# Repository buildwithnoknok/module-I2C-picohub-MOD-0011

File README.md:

# module-I2C-picohub-MOD-0011 — noknok PicoHub

**noknok ID: MOD-0011.** The noknok PicoHub: a carrier board for the Raspberry Pi Pico 2 W (the noknok
brain) with its own power manager. Status: rev 1.0 built and brought up (October 2026); power-manager
firmware v0.3.1, updatable over I2C from the brain (noknok I2C bootloader, flash layout 3).

## What it is

- **Power in:** USB-C on J1, any charger. A plain 5 V adapter runs the board (enough for small
  products); a USB-PD charger is asked for 9 V by default and up to 20 V / 3 A (60 W, any ordinary
  cable) when the load or a mezzanine needs it.
- **Power manager:** a CH32X035 that negotiates USB-PD, switches every rail, watches input current,
  temperature and the 5 V rail, and protects the board. To the brain it is an ordinary noknok I2C
  module (type `0x07`) on bus A. The board also works with no firmware on it, at 5 V.
- **Ports:** four Qwiic / STEMMA QT compatible I2C ports on two switchable buses (J3/J4 bus A,
  J5/J6 bus B, 3.3 V), a switched 5 V USB host port (J2, USB 2.0 full speed via the Pico's PIO-USB),
  and a bottom-side four-cluster pogo-pad interface for swappable **mezzanine** boards (raw PD power,
  switched 5 V, I2C, SPI, USB).
- Single-sided assembly, flat bottom, 80 × 40 mm, no electrolytic capacitors.

## Repo contents

| Path | Contents |
| --- | --- |
| `docs/spec.md` | The specification: power tree and budgets, X035 and Pico pin maps (as built), socket overview (§5b: voltage, current and what can be switched per connector), the **mezzanine interface** (§6, frozen: pin map, geometry, design rules), key parts |
| `hardware/kicad/` | KiCad project: schematic (3 sheets) and PCB. Custom symbols and footprints are embedded; the shared noknok KiCad library is in the [Ecosystem](https://github.com/buildwithnoknok/Ecosystem) repo (`electrical/`) |
| `hardware/MOD-0011-schematic.pdf` | Schematic as PDF |
| `hardware/MOD-0011-bom.csv` | Bill of materials: designators, manufacturer part numbers, LCSC codes |
| `firmware/` | Power-manager firmware (ch32fun): source, binaries, `index.json` for updates, test and debug tools. **The I2C command map is in [`firmware/readme.md`](firmware/readme.md).** `firmware/bringup/` holds the bring-up and diagnostics firmware |
| `mechanical/housing.json` | Housing profile (outline, mounting holes, connector positions and exits, heights, vent) for the [noknok housing configurator](https://buildwithnoknok.github.io/housing-configurator/), taken from the rev 1.0 KiCad PCB |
| `CHANGELOG.md` | Version history |

## Using it

- Brain pins (set in the brain's `settings.toml`): I2C bus A = GP10 (SDA) / GP11 (SCL), bus B =
  GP20 / GP21, PIO-USB = GP0 (D+) / GP1 (D−).
- The brain library `noknok.py` ([brain-Pico](https://github.com/buildwithnoknok/brain-Pico))
  finds the power manager during enumeration like any other module and offers it as `c.picohub`
  (`noknok.py` 1.16+): `status()`, `source_caps()`, `set_rail()`, `cycle_rail()`, `reset_pico()`,
  `set_min_input_voltage()`, `clear_faults()`. API: brain-Pico README → *noknok PicoHub power
  manager*; the protocol underneath: [`firmware/readme.md`](firmware/readme.md) → *I2C interface*.
- Designing a mezzanine: start with `docs/spec.md` §6. A mezzanine powered from cluster A must gate its
  load with MEZZ_EN and start safely on anything from 5 to 20 V.

## License

- Firmware / code: MIT — see [LICENSE](LICENSE).
- Hardware (schematics, PCB layout, fab files, docs): CC BY-SA 4.0 — see [LICENSE-hardware](LICENSE-hardware).
- `firmware/src/usbpd.h` is adapted from [ch32fun](https://github.com/cnlohr/ch32fun) (MIT).

## Trademarks

**noknok** is a registered trademark in Switzerland (Swissreg 1300007033).

Qwiic is a registered trademark of SparkFun Electronics, Inc. STEMMA QT is a trademark of Adafruit
Industries, LLC. Raspberry Pi and Pico are trademarks of Raspberry Pi Ltd. They are named here only to
state compatibility - noknok is not affiliated with, endorsed by, or sponsored by these companies.

## Safety & Liability

noknok hardware is an electronic device and a DIY/maker kit. You assemble, modify, flash, power, and
operate it at your own risk, and it is provided as is, without warranty. This board handles up to
20 V / 3 A. See the full notice: [License, Safety & Liability](https://buildwithnoknok.github.io/safety-and-license/).

Built with the help of AI. More about how noknok uses AI: [buildwithnoknok.github.io/safety-and-license](https://buildwithnoknok.github.io/safety-and-license/).

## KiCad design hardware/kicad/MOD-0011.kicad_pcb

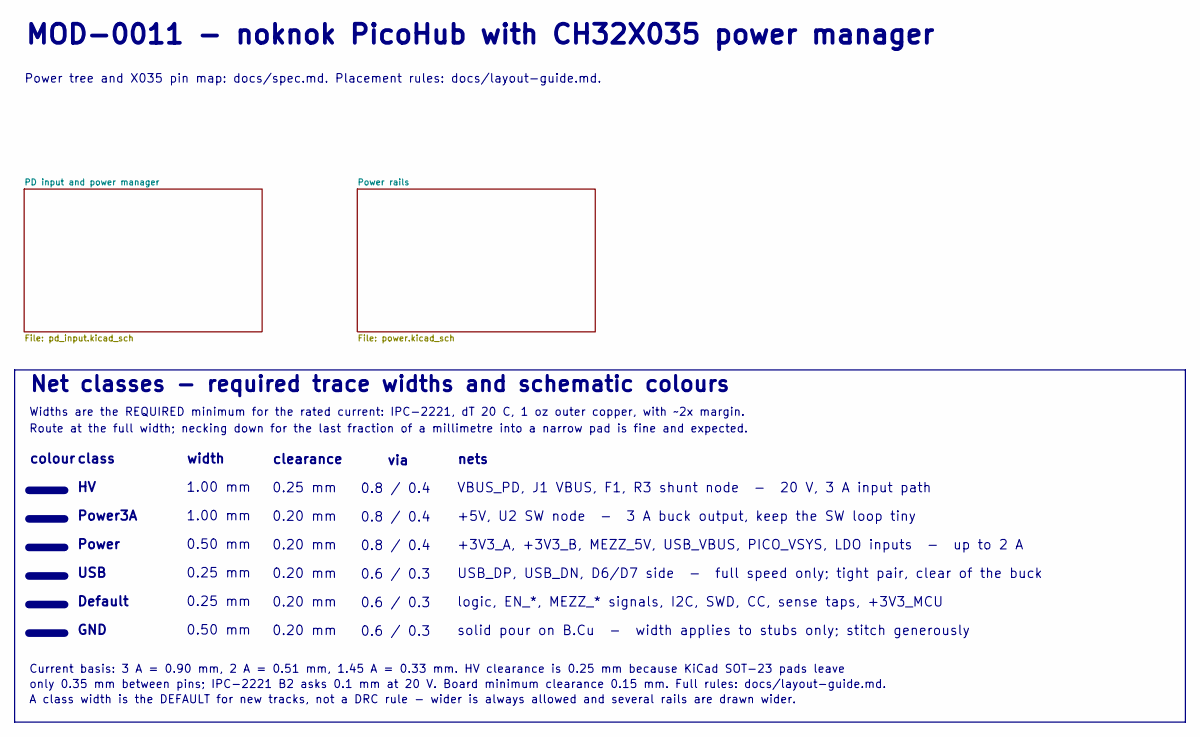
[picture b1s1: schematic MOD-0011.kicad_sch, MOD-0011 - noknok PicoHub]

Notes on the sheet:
Current basis: 3 A = 0.90 mm, 2 A = 0.51 mm, 1.45 A = 0.33 mm. HV clearance is 0.25 mm because KiCad SOT-23 pads leave
width
Power tree and X035 pin map: docs/spec.md. Placement rules: docs/layout-guide.md.
Net classes - required trace widths and schematic colours
USB
0.6 / 0.3
GND
USB_DP, USB_DN, D6/D7 side - full speed only; tight pair, clear of the buck
solid pour on B.Cu - width applies to stubs only; stitch generously
0.20 mm
class
+5V, U2 SW node - 3 A buck output, keep the SW loop tiny
1.00 mm
Default
A class width is the DEFAULT for new tracks, not a DRC rule - wider is always allowed and several rails are drawn wider.
VBUS_PD, J1 VBUS, F1, R3 shunt node - 20 V, 3 A input path
0.50 mm
0.25 mm
MOD-0011 - noknok PicoHub with CH32X035 power manager
clearance
via
+3V3_A, +3V3_B, MEZZ_5V, USB_VBUS, PICO_VSYS, LDO inputs - up to 2 A
0.8 / 0.4
colour
logic, EN_*, MEZZ_* signals, I2C, SWD, CC, sense taps, +3V3_MCU
Power3A
nets
only 0.35 mm between pins; IPC-2221 B2 asks 0.1 mm at 20 V. Board minimum clearance 0.15 mm. Full rules: docs/layout-guide.md.
Widths are the REQUIRED minimum for the rated current: IPC-2221, dT 20 C, 1 oz outer copper, with ~2x margin.
Power
Route at the full width; necking down for the last fraction of a millimetre into a narrow pad is fine and expected.

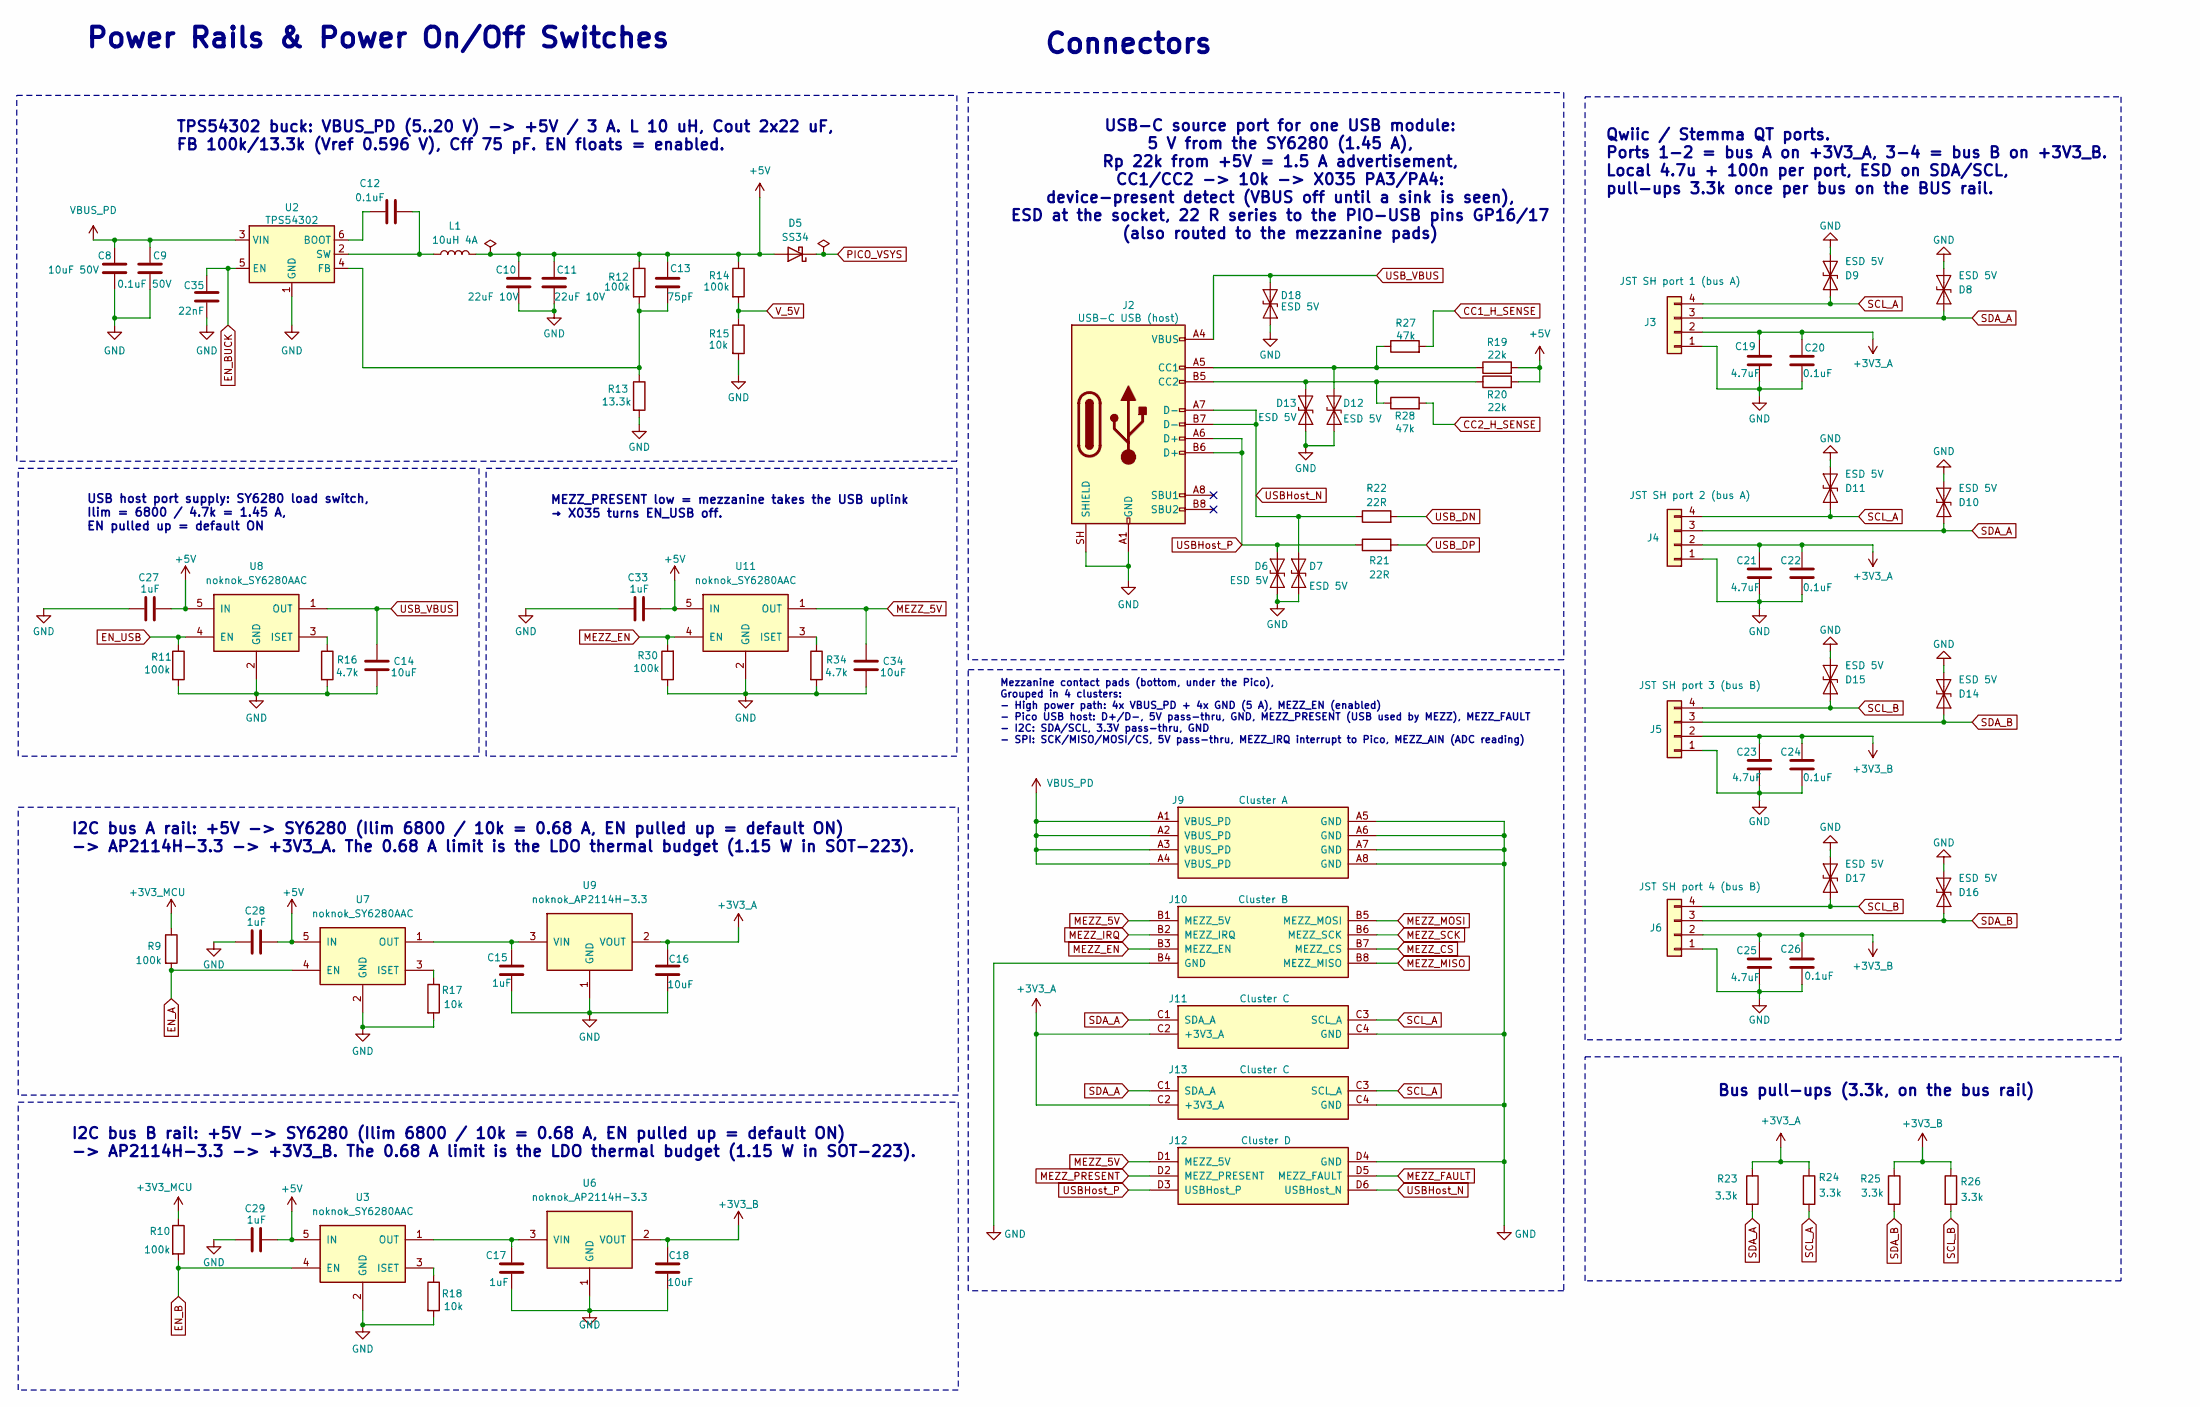
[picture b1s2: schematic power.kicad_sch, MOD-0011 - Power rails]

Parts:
C8: 10uF 50V; C_1210_3225Metric; LCSC Part # C138687
C9: 0.1uF 50V; C_0603_1608Metric; LCSC Part # C14663
C10, C11: 22uF 10V; C_0805_2012Metric; LCSC Part # C29277
C12, C20, C22, C24, C26: 0.1uF; C_0603_1608Metric; LCSC Part # C14663
C13: 75pF; C_0603_1608Metric; LCSC Part # C1681
C14, C16, C18, C34: 10uF; C_0805_2012Metric; LCSC Part # C15850
C15, C17, C27, C28, C29, C33: 1uF; C_0603_1608Metric; LCSC Part # C5199872
C19, C21, C23, C25: 4.7uF; C_0805_2012Metric; LCSC Part # C1779
C35: 22nF; C_0603_1608Metric; LCSC Part # C21122
D5: SS34; D_SMA; LCSC Part # C8678
D6, D7, D8, D9, D10, D11, D12, D13, D14, D15, D16, D17, D18: ESD 5V; D_SOD-923; LCSC Part # C111566
J2: USB-C USB (host); USB_C_Receptacle_HRO_TYPE-C-31-M-12; LCSC Part # C165948
J3: JST SH port 1 (bus A); JST_SH_SM04B-SRSS-TB_1x04-1MP_P1.00mm_Horizontal; LCSC Part # C160404
J4: JST SH port 2 (bus A); JST_SH_SM04B-SRSS-TB_1x04-1MP_P1.00mm_Horizontal; LCSC Part # C160404
J5: JST SH port 3 (bus B); JST_SH_SM04B-SRSS-TB_1x04-1MP_P1.00mm_Horizontal; LCSC Part # C160404
J6: JST SH port 4 (bus B); JST_SH_SM04B-SRSS-TB_1x04-1MP_P1.00mm_Horizontal; LCSC Part # C160404
J9: Cluster A; noknok_Mezzanine_A_Pads_M2.5
J10: Cluster B; noknok_Mezzanine_B_Pads_M2.5
J11, J13: Cluster C; noknok_Mezzanine_C_Pads_M2.5
J12: Cluster D; noknok_Mezzanine_D_Pads_M2.5
L1: 10uH 4A; L_Chilisin_BMRx00060630; LCSC Part # C2981193
R9, R10, R11, R12, R14, R30: 100k; R_0603_1608Metric; LCSC Part # C25803
R13: 13.3k; R_0603_1608Metric; LCSC Part # C25952
R15, R17, R18: 10k; R_0603_1608Metric; LCSC Part # C25804
R16, R34: 4.7k; R_0603_1608Metric; LCSC Part # C23162
R19, R20: 22k; R_0603_1608Metric; LCSC Part # C31850
R21, R22: 22R; R_0603_1608Metric; LCSC Part # C23345
R23, R24, R25, R26: 3.3k; R_0603_1608Metric; LCSC Part # C22978
R27, R28: 47k; R_0603_1608Metric; LCSC Part # C25819
U2: TPS54302; TSOT-23-6; LCSC Part # C311983
U3, U7, U8, U11: noknok_SY6280AAC; SOT-23-5; LCSC Part # C55136
U6, U9: noknok_AP2114H-3.3; SOT-223-3_TabPin2; LCSC Part # C150716

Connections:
+3V3_A: C16.1, C19.1, C20.1, C21.1, C22.1, J3.2, J4.2, J11.C2 (+3V3_A), J13.C2 (+3V3_A), R23.1, R24.1, U9.2 (VOUT)
+3V3_B: C18.1, C23.1, C24.1, C25.1, C26.1, J5.2, J6.2, R25.1, R26.1, U6.2 (VOUT)
+3V3_MCU: R9.1, R10.1; also elsewhere on the board
CC1_H_SENSE: R27.2; also elsewhere on the board
CC2_H_SENSE: R28.2; also elsewhere on the board
EN_A: R9.2, U7.4 (EN); also elsewhere on the board
EN_B: R10.2, U3.4 (EN); also elsewhere on the board
EN_BUCK: C35.1, U2.5 (EN); also elsewhere on the board
EN_USB: R11.1, U8.4 (EN); also elsewhere on the board
MEZZ_5V: C34.2, J10.B1 (MEZZ_5V), J12.D1 (MEZZ_5V), U11.1 (OUT)
MEZZ_CS: J10.B7 (MEZZ_CS); also elsewhere on the board
MEZZ_EN: J10.B3 (MEZZ_EN), R30.2, U11.4 (EN); also elsewhere on the board
MEZZ_FAULT: J12.D5 (MEZZ_FAULT); also elsewhere on the board
MEZZ_IRQ: J10.B2 (MEZZ_IRQ); also elsewhere on the board
MEZZ_MISO: J10.B8 (MEZZ_MISO); also elsewhere on the board
MEZZ_MOSI: J10.B5 (MEZZ_MOSI); also elsewhere on the board
MEZZ_PRESENT: J12.D2 (MEZZ_PRESENT); also elsewhere on the board
MEZZ_SCK: J10.B6 (MEZZ_SCK); also elsewhere on the board
unnamed: D12.1 (A1), J2.A5 (CC1), R19.1, R27.1
unnamed: D13.1 (A1), J2.B5 (CC2), R20.1, R28.1
unnamed: C12.1, U2.6 (BOOT)
unnamed: C13.2, R12.2, R13.1, U2.4 (FB)
unnamed: C12.2, L1.1, U2.2 (SW)
unnamed: R18.1, U3.3 (ISET)
unnamed: C17.1, U3.1 (OUT), U6.3 (VIN)
unnamed: R17.1, U7.3 (ISET)
unnamed: C15.1, U7.1 (OUT), U9.3 (VIN)
unnamed: R16.1, U8.3 (ISET)
unnamed: R34.1, U11.3 (ISET)
SCL_A: D9.1 (A1), D11.1 (A1), J3.4, J4.4, J11.C3 (SCL_A), J13.C3 (SCL_A), R24.2; also elsewhere on the board
SCL_B: D15.1 (A1), D17.1 (A1), J5.4, J6.4, R26.2; also elsewhere on the board
SDA_A: D8.1 (A1), D10.1 (A1), J3.3, J4.3, J11.C1 (SDA_A), J13.C1 (SDA_A), R23.2; also elsewhere on the board
SDA_B: D14.1 (A1), D16.1 (A1), J5.3, J6.3, R25.2; also elsewhere on the board
USBHost_N: D7.1 (A1), J2.A7 (D-), J2.B7 (D-), J12.D6 (USBHost_N), R22.1
USBHost_P: D6.1 (A1), J2.A6 (D+), J2.B6 (D+), J12.D3 (USBHost_P), R21.1
USB_DN: R22.2; also elsewhere on the board
USB_DP: R21.2; also elsewhere on the board
USB_VBUS: C14.2, D18.1 (A1), J2.A4 (VBUS), J2.A9 (VBUS), J2.B4 (VBUS), J2.B9 (VBUS), U8.1 (OUT)
V_5V: R14.2, R15.1; also elsewhere on the board

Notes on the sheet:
Connectors
TPS54302 buck: VBUS_PD (5..20 V) -> +5V / 3 A. L 10 uH, Cout 2x22 uF, FB 100k/13.3k (Vref 0.596 V), Cff 75 pF. EN floats = enabled.
Qwiic / Stemma QT ports. Ports 1-2 = bus A on +3V3_A, 3-4 = bus B on +3V3_B. Local 4.7u + 100n per port, ESD on SDA/SCL, pull-ups 3.3k once per bus on the BUS rail.
I2C bus A rail: +5V -> SY6280 (Ilim 6800 / 10k = 0.68 A, EN pulled up = default ON) -> AP2114H-3.3 -> +3V3_A. The 0.68 A limit is the LDO thermal budget (1.15 W in SOT-223).
USB-C source port for one USB module: 5 V from the SY6280 (1.45 A), Rp 22k from +5V = 1.5 A advertisement, CC1/CC2 -> 10k -> X035 PA3/PA4: device-present detect (VBUS off until a sink is seen), ESD at the socket, 22 R series to the PIO-USB pins GP16/17 (also routed to the mezzanine pads)
USB host port supply: SY6280 load switch, Ilim = 6800 / 4.7k = 1.45 A, EN pulled up = default ON
Power Rails & Power On/Off Switches
Bus pull-ups (3.3k, on the bus rail)
MEZZ_PRESENT low = mezzanine takes the USB uplink → X035 turns EN_USB off.
Mezzanine contact pads (bottom, under the Pico), Grouped in 4 clusters: - High power path: 4x VBUS_PD + 4x GND (5 A), MEZZ_EN (enabled) - Pico USB host: D+/D-, 5V pass-thru, GND, MEZZ_PRESENT (USB used by MEZZ), MEZZ_FAULT - I2C: SDA/SCL, 3.3V pass-thru, GND - SPI: SCK/MISO/MOSI/CS, 5V pass-thru, M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
I2C bus B rail: +5V -> SY6280 (Ilim 6800 / 10k = 0.68 A, EN pulled up = default ON) -> AP2114H-3.3 -> +3V3_B. The 0.68 A limit is the LDO thermal budget (1.15 W in SOT-223).

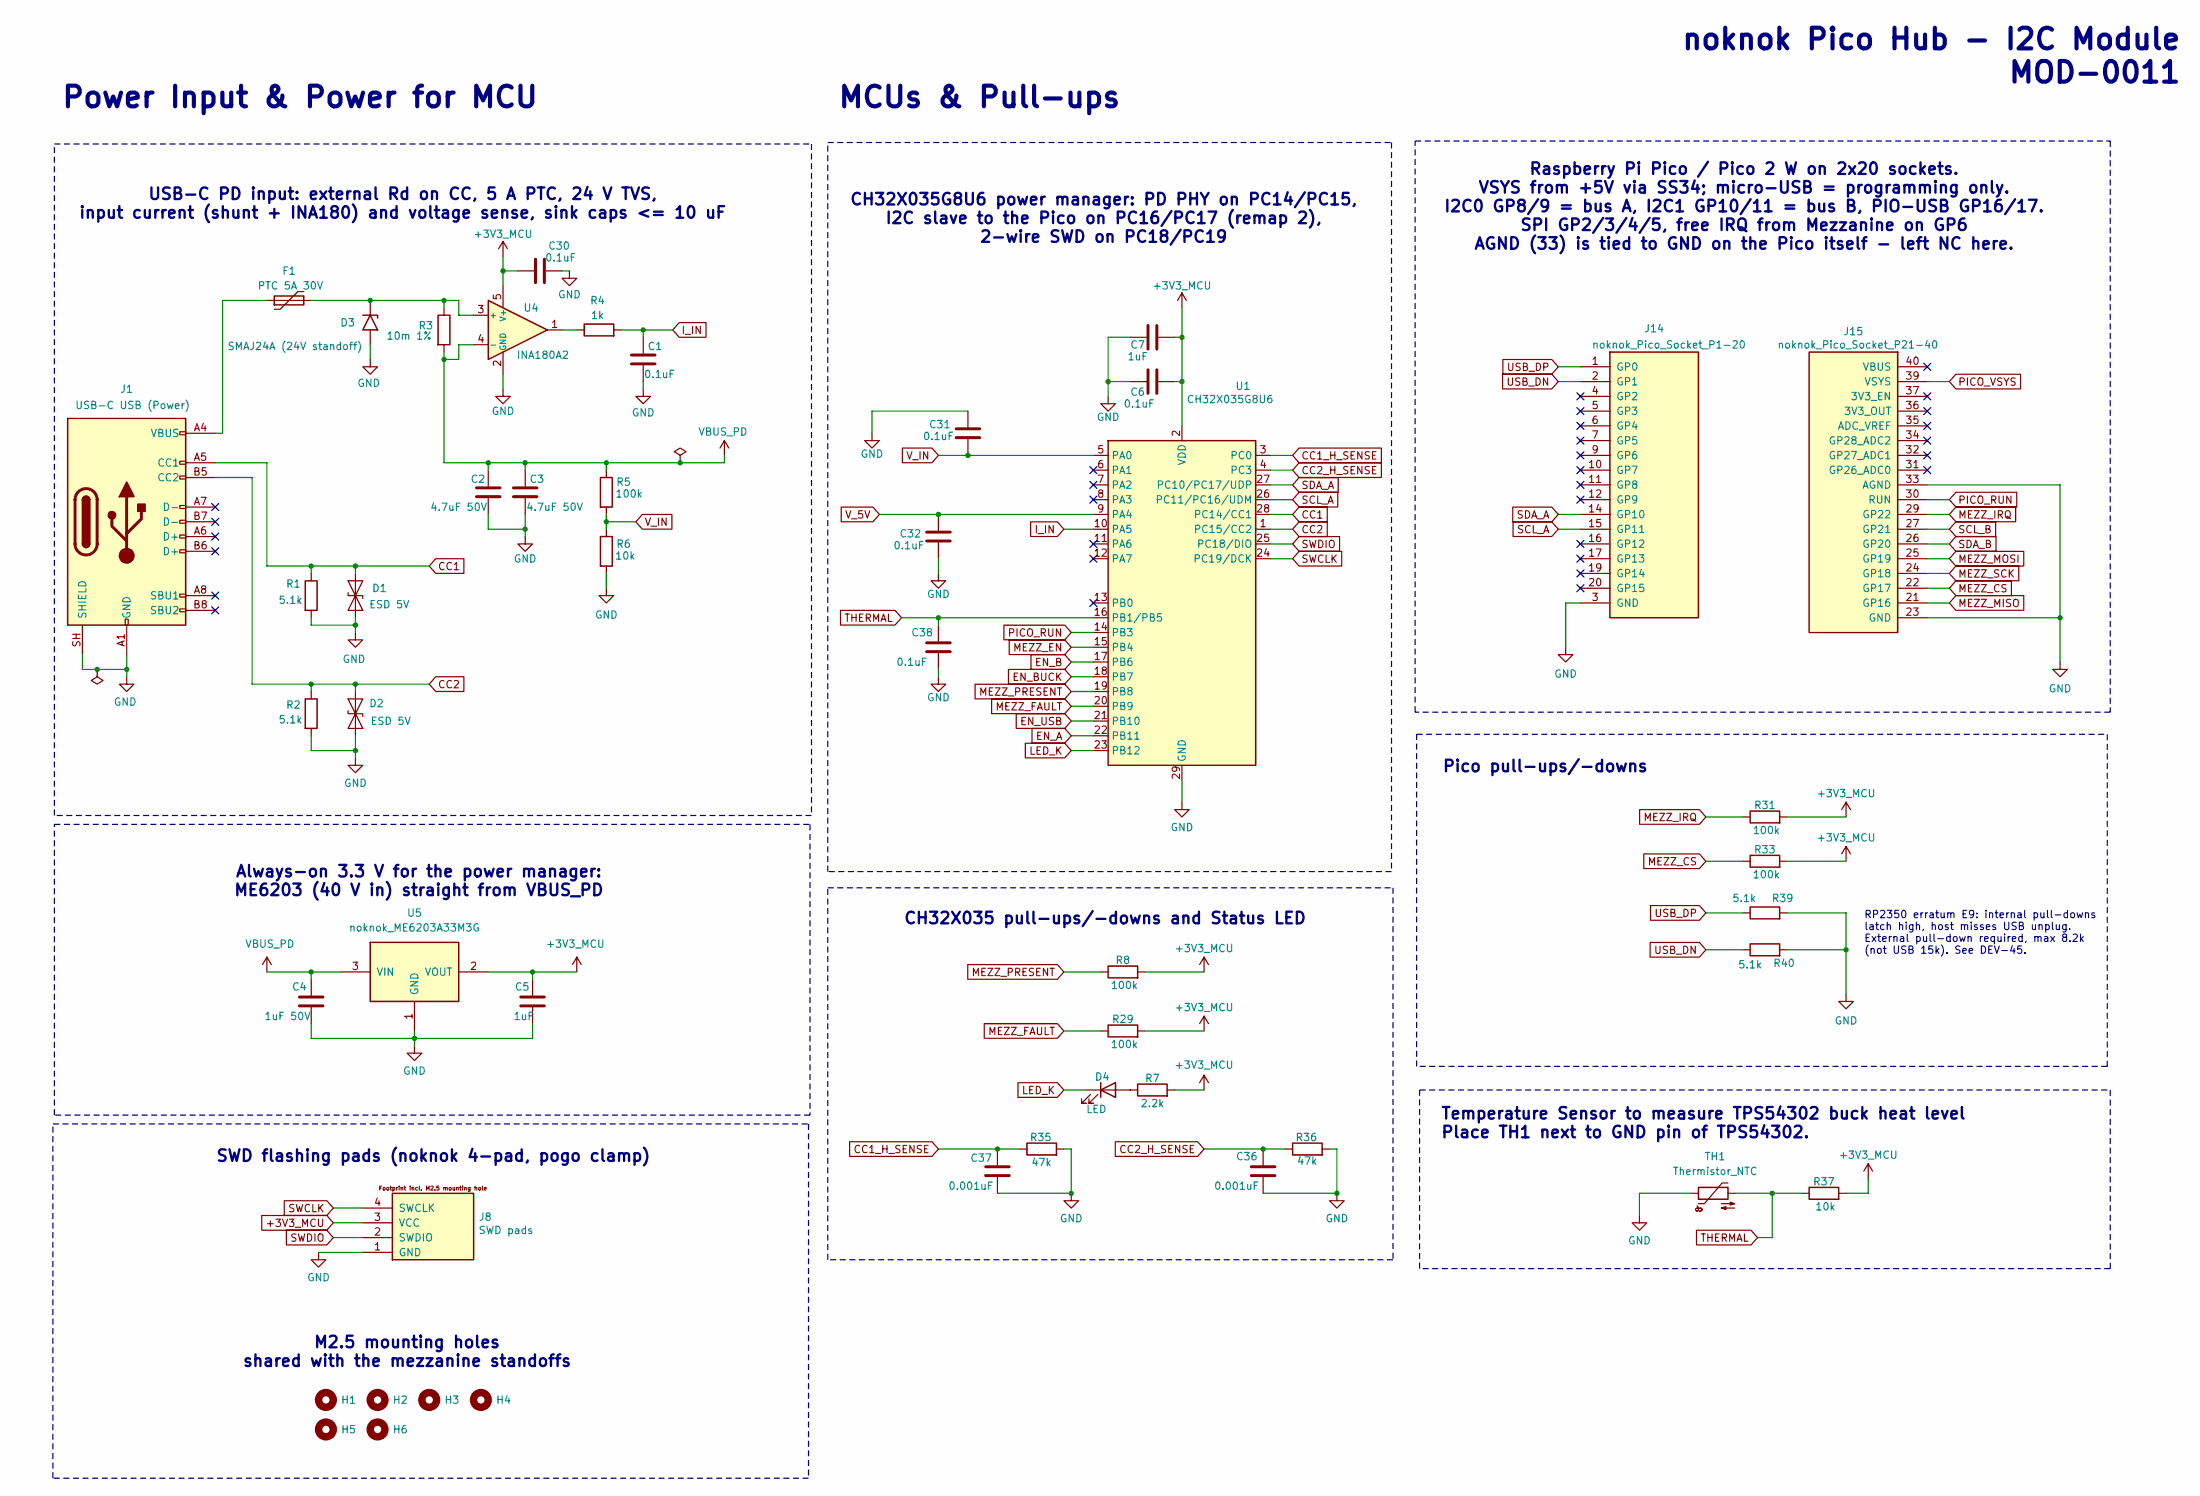
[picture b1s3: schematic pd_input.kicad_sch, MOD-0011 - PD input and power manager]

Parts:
C1, C6, C30, C31, C32, C38: 0.1uF; C_0603_1608Metric; LCSC Part # C14663
C2, C3: 4.7uF 50V; C_1206_3216Metric; LCSC Part # C51205
C4: 1uF 50V; C_0603_1608Metric; LCSC Part # C5199872
C5, C7: 1uF; C_0603_1608Metric; LCSC Part # C5199872
C36, C37: 0.001uF; C_0603_1608Metric; LCSC Part # C1588
D1, D2: ESD 5V; D_SOD-923; LCSC Part # C111566
D3: SMAJ24A (24V standoff); D_SMA; LCSC Part # C908774
D4: LED; LED_0603_1608Metric; LCSC Part # C2286
F1: PTC 5A 30V; Fuse_2920_7451Metric; LCSC Part # C19078763
H1, H2, H3, H4, H5, H6: noknok_MountingHole; noknok_MountingHole_2.5mm_M2.5
J1: USB-C USB (Power); USB_C_Receptacle_HRO_TYPE-C-31-M-12; LCSC Part # C165948
J8: SWD pads; noknok_FlashPads_USB-module_1x4_M2.5
J14: noknok_Pico_Socket_P1-20; noknok_Pico_Socket_P1-20_THT; LCSC Part # C7509519
J15: noknok_Pico_Socket_P21-40; noknok_Pico_Socket_P21-40_THT; LCSC Part # C7509519
R1, R2: 5.1k; R_0603_1608Metric; LCSC Part # C23186
R3: 10m 1%; R_2512_6332Metric; LCSC Part # C46634450
R4: 1k; R_0603_1608Metric; LCSC Part # C21190
R5, R8, R29, R31, R33: 100k; R_0603_1608Metric; LCSC Part # C25803
R6, R37: 10k; R_0603_1608Metric; LCSC Part # C25804
R7: 2.2k; R_0603_1608Metric; LCSC Part # C4190
R35, R36: 47k; R_0603_1608Metric; LCSC Part # C25819
R39, R40: 5.1k; R_0603_1608Metric; LCSC Part # C21190
TH1: Thermistor_NTC; R_0603_1608Metric; LCSC Part # C2892547
U1: CH32X035G8U6; WQFN-28-1EP_4x4mm_P0.4mm_EP2.7x2.7mm; LCSC Part # C7437027
U4: INA180A2; SOT-23-5; LCSC Part # C192764
U5: noknok_ME6203A33M3G; SOT-23; LCSC Part # C87842

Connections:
+3V3_MCU: C5.1, C6.2, C7.2, C30.1, J8.3 (VCC), R7.2, R8.2, R29.2, R31.2, R33.2, R37.2, U1.2 (VDD), U4.5 (V+), U5.2 (VOUT); also elsewhere on the board
CC1: D1.1 (A1), J1.A5 (CC1), R1.1, U1.28 (PC14/CC1)
CC1_H_SENSE: C37.1, R35.1, U1.3 (PC0); also elsewhere on the board
CC2: D2.1 (A1), J1.B5 (CC2), R2.1, U1.1 (PC15/CC2)
CC2_H_SENSE: C36.1, R36.1, U1.4 (PC3); also elsewhere on the board
EN_A: U1.22 (PB11); also elsewhere on the board
EN_B: U1.17 (PB6); also elsewhere on the board
EN_BUCK: U1.18 (PB7); also elsewhere on the board
EN_USB: U1.21 (PB10); also elsewhere on the board
I_IN: C1.1, R4.2, U1.10 (PA5)
LED_K: D4.1 (K), U1.23 (PB12)
MEZZ_CS: J15.22 (GP17), R33.1; also elsewhere on the board
MEZZ_EN: U1.15 (PB4); also elsewhere on the board
MEZZ_FAULT: R29.1, U1.20 (PB9); also elsewhere on the board
MEZZ_IRQ: J15.29 (GP22), R31.1; also elsewhere on the board
MEZZ_MISO: J15.21 (GP16); also elsewhere on the board
MEZZ_MOSI: J15.25 (GP19); also elsewhere on the board
MEZZ_PRESENT: R8.1, U1.19 (PB8); also elsewhere on the board
MEZZ_SCK: J15.24 (GP18); also elsewhere on the board
unnamed: D3.1 (A1), F1.2, R3.1, U4.3 (+)
unnamed: D4.2 (A), R7.1
unnamed: F1.1, J1.A4 (VBUS), J1.A9 (VBUS), J1.B4 (VBUS), J1.B9 (VBUS)
unnamed: R4.1, U4.1
PICO_RUN: J15.30 (RUN), U1.14 (PB3)
SCL_A: J14.15 (GP11), U1.26 (PC11/PC16/UDM); also elsewhere on the board
SCL_B: J15.27 (GP21); also elsewhere on the board
SDA_A: J14.14 (GP10), U1.27 (PC10/PC17/UDP); also elsewhere on the board
SDA_B: J15.26 (GP20); also elsewhere on the board
SWCLK: J8.4 (SWCLK), U1.24 (PC19/DCK)
SWDIO: J8.2 (SWDIO), U1.25 (PC18/DIO)
THERMAL: C38.1, R37.1, TH1.2, U1.16 (PB1/PB5)
USB_DN: J14.2 (GP1), R40.1; also elsewhere on the board
USB_DP: J14.1 (GP0), R39.1; also elsewhere on the board
V_5V: C32.2, U1.9 (PA4); also elsewhere on the board
V_IN: C31.1, R5.2, R6.1, U1.5 (PA0)

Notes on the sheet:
RP2350 erratum E9: internal pull-downs latch high, host misses USB unplug. External pull-down required, max 8.2k (not USB 15k). See DEV-45.
Temperature Sensor to measure TPS54302 buck heat level Place TH1 next to GND pin of TPS54302.
Power Input & Power for MCU
Pico pull-ups/-downs
SWD flashing pads (noknok 4-pad, pogo clamp)
CH32X035G8U6 power manager: PD PHY on PC14/PC15, I2C slave to the Pico on PC16/PC17 (remap 2), 2-wire SWD on PC18/PC19
Raspberry Pi Pico / Pico 2 W on 2x20 sockets. VSYS from +5V via SS34; micro-USB = programming only. I2C0 GP8/9 = bus A, I2C1 GP10/11 = bus B, PIO-USB GP16/17. SPI GP2/3/4/5, free IRQ from Mezzanine on GP6 AGND (33) is tied to GND on the Pico itself - left NC here.
MCUs & Pull-ups
USB-C PD input: external Rd on CC, 5 A PTC, 24 V TVS, input current (shunt + INA180) and voltage sense, sink caps <= 10 uF
M2.5 mounting holes shared with the mezzanine standoffs
CH32X035 pull-ups/-downs and Status LED
Always-on 3.3 V for the power manager: ME6203 (40 V in) straight from VBUS_PD
noknok Pico Hub - I2C Module MOD-0011

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
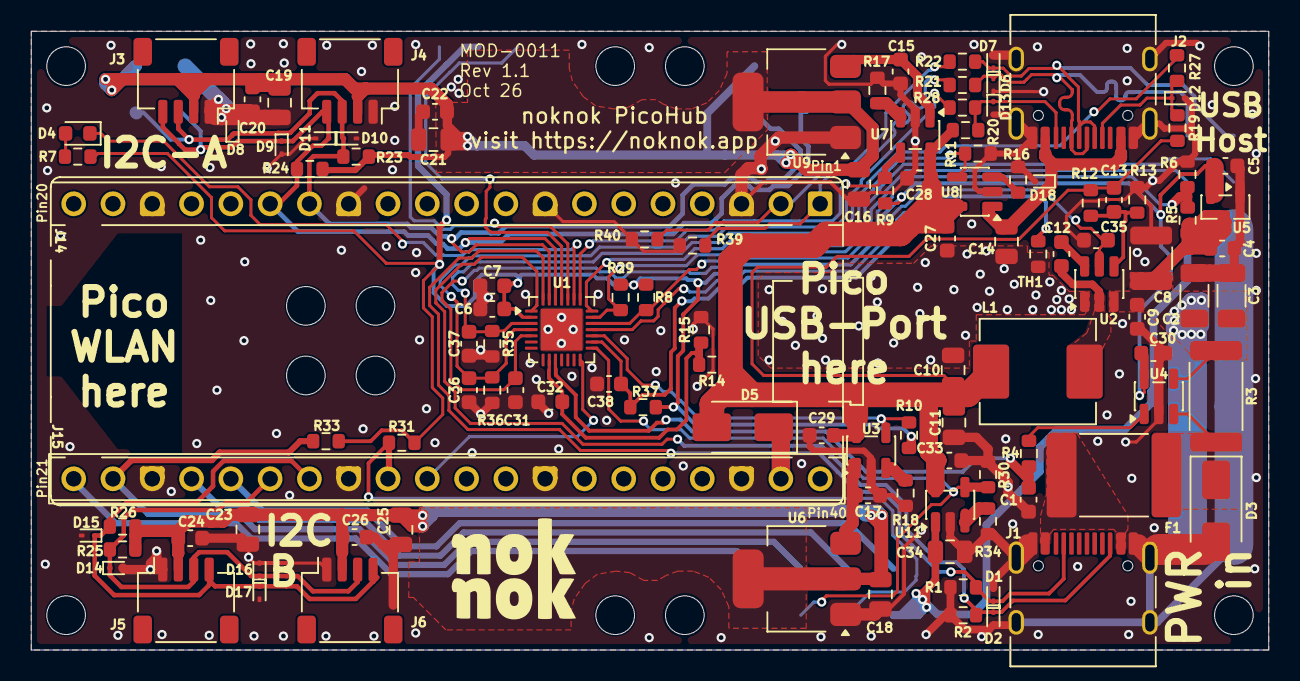
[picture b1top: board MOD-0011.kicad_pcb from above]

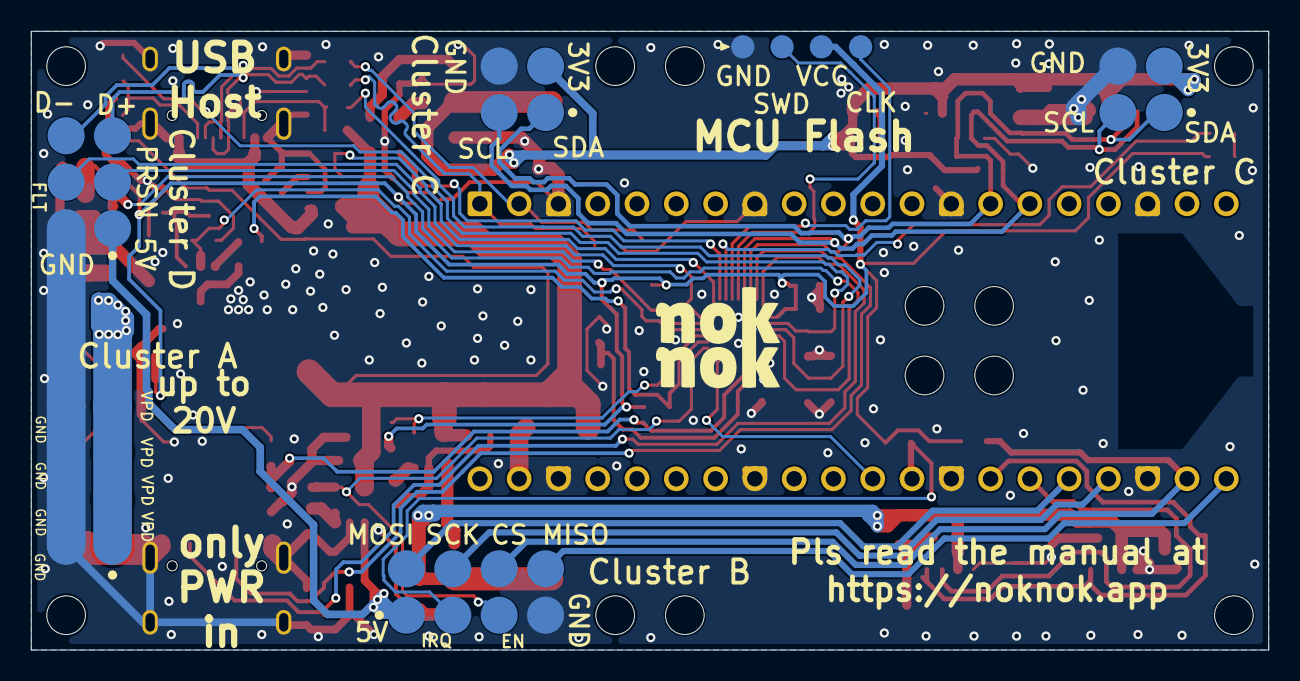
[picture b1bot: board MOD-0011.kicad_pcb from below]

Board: 2 copper layers, 80.0 x 40.0 mm, 127 parts (6 on the bottom side), 56 nets.

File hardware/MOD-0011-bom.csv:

Item #,Designator,Qty,Manufacturer,Mfg Part #,Description / Value,Vendor Part #,Note
1,"C1, C6, C9, C12, C20, C22, C24, C26, C30, C31, C32, C38",12,YAGEO,CC0603KRX7R9BB104,0.1uF ±10% 50V X7R 0603,C14663,one 50 V reel for every 0.1 uF; Samsung CL10B104KB8NNNC C1591 (16-LED board) is out of stock at LCSC today
2,"C2, C3",2,Samsung,CL31B475KBHNNNE,4.7uF ±10% 50V X7R 1206,C51205,"PD input caps (sink capacitance <= 10 uF). Moved 1210 -> 1206 on 24 Sep: same X7R/50 V, 36% less area, 45% cheaper; ~10% more DC-bias loss, irrelevant here"
3,"C4, C5, C7, C15, C17, C27, C28, C29, C33",9,Samsung,CL10B105KB8NQNC,1uF ±10% 50V X7R 0603,C5199872,C4 (ME6203 input); same reel as the other 1 uF; same part as the 16-LED board
4,C8,1,Samsung,CL32B106KBJNNNE,10uF ±10% 50V X7R 1210,C138687,buck input cap
5,"C10, C11",2,Samsung,CL21A226MPQNNNE,22uF ±20% 10V X5R 0805,C29277,buck output caps; alt FOJAN FCC0805X226M100FT C5137600 (146k stock)
6,C13,1,FH,0603CG750J500NT,75pF ±5% 50V C0G 0603,C1681,Samsung CL10C750JB8NNNC is discontinued
7,"C14, C16, C18, C34",4,Samsung,CL21A106KAYNNNE,10uF ±10% 25V X5R 0805,C15850,LDO outputs
8,"C19, C21, C23, C25",4,Samsung,CL21A475KAQNNNE,4.7uF ±10% 25V X5R 0805,C1779,port bulk caps
9,C35,1,Samsung,CL10B223KB8NNNC,22nF ±10% 50V X7R 0603,C21122,TPS54302 EN delay cap (~38 ms default-on)
10,"C36, C37",2,Samsung,CL10B102KB8NNNC,1nF ±10% 50V X7R 0603,C1588,ADC filter at PA3/PA4
11,"D1, D2, D6, D7, D8, D9, D10, D11, D12, D13, D14, D15, D16, D17, D18",15,onsemi,ESD9B5.0ST5G,"ESD TVS 5V working, SOD-923",C111566,same part as the 16-LED board
12,D3,1,GOODWORK,SMAJ24A,"TVS 24V standoff, 38.9V clamp, 400W, SMA, unidirectional",C908774,MDD C113962 out of stock; Littelfuse C148222 as a name-brand alternative
13,D4,1,Hubei KENTO,KT-0603R,LED red 0603,C2286,the noknok status LED
14,D5,1,MDD,SS34,Schottky 40V 3A SMA,C8678,VSYS OR-ing diode
15,F1,1,LUTE,2920L500/30GR,"PTC resettable fuse 5A hold, 30V, 2920",C19078763,"30 V (was 24 V): more headroom on the PD voltage steps, cheaper, 47k in stock vs 18k. Hold current derates to ~3.5 A at 60 C ambient - see spec 2.1"
16,"J1, J2",2,HRO,TYPE-C-31-M-12,"USB-C receptacle 16-pin, 20V/5A, 10k cycles",C165948,host port; PD input
17,"J3, J4, J5, J6",4,JST,SM04B-SRSS-TB(LF)(SN),JST SH 4-pin horizontal (Qwiic),C160404,same as all modules
18,"J14, J15",2,CONNFLY,DS1023-1x20SF11,"Female header 1x20, 2.54 mm, THT, 8.5 mm insulator, gold — Pico socket half (J14 = pins 1-20, J15 = pins 21-40)",C7509519,one of the two socket halves (J14/J15); the Pico 2 W (SC1633) is bought separately and plugged in. Split into two designators so the position file reports two correct centroids - JLCPCB rejected the single-footprint version.
19,L1,1,Chilisin,AMRU00060630100MA1,"10uH moulded power inductor, Isat 4A, 7.3x6.8mm",C2981193,buck inductor
20,"R1, R2, R39, R40",4,UNI-ROYAL,0603WAF5101T5E,5.1k ±1% 0603,C23186,"R1/R2 PD Rd, 1% needed. R39/R40 USB D+/D- pull-downs (rev 1.1, RP2350 erratum E9, keep <= 8.2k, DEV-45)"
21,R3,1,JIERR,JER2512F3R010,"10mOhm ±1% 3W alloy current-sense resistor 2512, ±50ppm",C46634450,input shunt for the INA180A2
22,R4,1,UNI-ROYAL,0603WAF1001T5E,1k ±1% 0603,C21190,
23,"R5, R8, R9, R10, R11, R12, R14, R29, R30, R31, R33",11,UNI-ROYAL,0603WAF1003T5E,100k ±1% 0603,C25803,1% because R5 is the buck feedback top resistor
24,"R6, R15, R17, R18, R37",5,UNI-ROYAL,0603WAF1002T5E,10k ±1% 0603,C25804,
25,R7,1,UNI-ROYAL,0603WAF2201T5E,2.2k ±1% 0603,C4190,status LED
26,R13,1,UNI-ROYAL,0603WAF1332T5E,13.3k ±1% 0603,C25952,buck feedback bottom
27,"R16, R34",2,UNI-ROYAL,0603WAF4701T5E,4.7k ±1% 0603,C23162,SY6280 Rset (1.45 A)
28,"R19, R20",2,UNI-ROYAL,0603WAF2202T5E,22k ±1% 0603,C31850,host-port Rp
29,"R21, R22",2,UNI-ROYAL,0603WAF220JT5E,22R ±1% 0603,C23345,USB D+/D- series
30,"R23, R24, R25, R26",4,UNI-ROYAL,0603WAF3301T5E,3.3k ±1% 0603,C22978,I2C pull-ups
31,"R27, R28, R35, R36",4,UNI-ROYAL,0603WAF4702T5E,47k ±1% 0603,C25819,host-port CC sense divider (R27/R28 series + R35/R36 to GND)
32,TH1,1,KUU,KNTC0603/10KF3950,"NTC thermistor 10k ±1%, B3950 (B25/85) ±1%, 0603, -40 to +125 C",C2892547,"board temperature sensor (TH1) beside U2; low leg of a 10k divider into X035 pin 16 (PB1/A9; corrected 18 Oct 2026, DEV-117)"
33,U1,1,WCH,CH32X035G8U6,"RISC-V MCU with USB-PD PHY, QFN-28",C7437027,power manager
34,U2,1,TI,TPS54302DDCR,"3A synchronous buck, 4.5-28V in, TSOT-23-6",C311983,5 V buck
35,"U3, U7, U8, U11",4,Silergy,SY6280AAC,"load switch with adjustable current limit, SOT-23-5",C55136,"USB host, bus A, bus B"
36,U4,1,TI,INA180A2IDBVR,"current-sense amplifier 50 V/V, SOT-23-5",C192764,input current
37,U5,1,Microne,ME6203A33M3G,"3.3V LDO, 40V in, SOT-23",C87842,always-on X035 supply
38,"U6, U9",2,Diodes Inc,AP2114H-3.3TRG1,"3.3V 1A LDO, SOT-223",C150716,bus A / bus B LDOs

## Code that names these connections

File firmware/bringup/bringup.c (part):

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 * power-manager firmware (DEV-85) is written:
 *
 *  1. BOOT / warm-reset test (runs by itself at power-on).
 *     PC17 is I2C SDA_A *and* the X035 BOOT-detect pin: high at reset may
 *     enter the factory bootloader. At a cold boot SDA_A's pull-up (R23 on
 *     +3V3_A) is still unpowered; at a warm reset it is not. Sequence, driven
 *     by the reset-cause flags so it needs no memory between resets:
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 *        software   -> LED 2 blinks x3, then a WATCHDOG reset (IWDG left unfed, ~5.6 s)
 *        watchdog   -> LED 3 blinks x3, then the heartbeat = PASS
 *     LED goes dark and stays dark after a reset = stuck in the bootloader = FAIL.
 *     If PC17 is LOW before a reset the test would prove nothing (bus A not
 *     powered, e.g. board fed only from the flash clamp): the LED fast-blinks
 *     and the test waits until PC17 is high.
 *
 *  2. Hardware default states: nothing below touches EN_A / EN_B / EN_USB /
 *     MEZZ_EN / EN_BUCK / PICO_RUN until a command is typed. Measure first.
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 *
 * Pin map = the board AS FABRICATED (read from hardware/kicad/MOD-0011.kicad_pcb,
 * U1 pads, 17 Oct 2026). docs/spec.md section 3 was rewritten from it on 18 Oct 2026.
 *   pin  3 PC0  A10  CC1_H_SENSE  J2 CC1 via 47k/47k        (A10/A13 to be
 *   pin  4 PC3  A13  CC2_H_SENSE  J2 CC2 via 47k/47k         confirmed: 'd')
 *   pin  5 PA0  A0   V_IN         100k/10k (x11)
 *   pin  9 PA4  A4   V_5V         100k/10k (x11)
 *   pin 10 PA5  A5   I_IN         INA180A2 on 10 mohm: 0.5 V per A
 *   pin 16 PB1  A9   THERMAL      NTC 10k B3950 (TH1) to GND, 10k (R37) to 3V3_MCU
 *   pin 14 PB3       PICO_RUN     open-drain ONLY (Pico RUN has its own pull-up)
 *   pin 15 PB4       MEZZ_EN      R30 100k pull-DOWN -> default OFF, drive high = on
 *   pin 17 PB6       EN_B         R10 100k pull-up   -> default ON, drive low = off
 *   pin 18 PB7       EN_BUCK      C35 22 nF, no pull -> buck self-starts; low = off
 *   pin 19 PB8       MEZZ_PRESENT pull-up, low = mezzanine takes the USB uplink
 *   pin 20 PB9       MEZZ_FAULT   pull-up, low = mezzanine fault
 *   pin 21 PB10      EN_USB       R11 100k pull-DOWN -> default OFF, drive high = on
 *   pin 22 PB11      EN_A         R9 100k pull-up    -> default ON, drive low = off
 *   pin 23 PB12      LED_K        status LED cathode, active LOW
 *   pin 27 PC17      SDA_A        read only here (BOOT-detect pin)
 */
#include "ch32fun.h"
#include <stdio.h>
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#define RST_LPWRF  (1u << 31)

// Port B pin numbers (all < 16, so funPinMode handles them).
#define P_PICO_RUN     PB3
#define P_MEZZ_EN      PB4
#define P_EN_B         PB6
#define P_EN_BUCK      PB7
#define P_MEZZ_PRESENT PB8
#define P_MEZZ_FAULT   PB9
#define P_EN_USB       PB10
#define P_EN_A         PB11
#define P_LED          PB12

// ADC channels
#define CH_V_IN   0
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	ADC1->CTLR2 |= ADC_ADON | ADC_EXTSEL;

	// analog mode (CFG = 0) on the six wired channels
	funPinMode( PA0, 0 ); funPinMode( PA4, 0 ); funPinMode( PA5, 0 );
	funPinMode( PB1, 0 ); funPinMode( PC0, 0 ); funPinMode( PC3, 0 );
}

static uint16_t adc_read( int ch )     // average of 16 conversions, 0..4095
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static void wait_sda_high( const char * why )
{
	if( sda_a_high() ) return;
	printf( "TEST INVALID until PC17/SDA_A is high (%s): bus A not powered? "
	        "Power the board from USB-C J1, not only from the flash clamp.\n", why );
	while( !sda_a_high() ) { led(1); Delay_Ms( 50 ); led(0); Delay_Ms( 50 ); }
	printf( "PC17 high now, continuing\n" );
}

static const char * cause_name( uint32_t f )
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// may issue on its way to the app.
#define BOOTLOG_MAGIC 0x4E4B4231u            // "NKB1"
#define BOOTLOG_MAX   16
typedef struct { uint32_t magic, count; uint32_t flags[BOOTLOG_MAX]; uint8_t pc17[BOOTLOG_MAX]; } bootlog_t;
#define BOOTLOG ((volatile bootlog_t *)0x20003000)

int main( void )
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	int cold = ( BOOTLOG->magic != BOOTLOG_MAGIC || BOOTLOG->count >= BOOTLOG_MAX );
	if( cold ) { BOOTLOG->magic = BOOTLOG_MAGIC; BOOTLOG->count = 0; }
	BOOTLOG->flags[BOOTLOG->count] = flags;
	BOOTLOG->pc17[BOOTLOG->count] = sda_a_high();
	BOOTLOG->count++;

	printf( "\nnoknok PicoHub MOD-0011 bring-up v" FW_VERSION "  reset flags 0x%08lx = %s  PC17 %d%s\n",
	        (unsigned long)flags, cause_name( flags ), sda_a_high(), cold ? "  (first boot since power-up)" : "" );
	printf( "boot log since power-up:" );
	for( uint32_t i = 0; i < BOOTLOG->count; i++ )
		printf( "  #%lu 0x%08lx %s PC17=%d", (unsigned long)i + 1, (unsigned long)BOOTLOG->flags[i],
		        cause_name( BOOTLOG->flags[i] ), BOOTLOG->pc17[i] );
	printf( "\n" );

	// On the X035 the factory bootloader runs at EVERY power-up and starts the app with a
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	{
		blink_code( 3 );
		printf( "RESET TEST PASS: power-on -> software reset -> watchdog reset, "
		        "app came back each time with PC17 high.\n" );
	}
	else if( flags & RST_SFTF )
	{
		blink_code( 2 );
		wait_sda_high( "before watchdog reset" );
		printf( "STEP 2/3 back from SOFTWARE reset. Watchdog reset in ~5.6 s (PC17 %d)\n", sda_a_high() );
		iwdg_start_unfed();
		while( 1 ) { led(1); Delay_Ms( 50 ); led(0); Delay_Ms( 450 ); }
	}
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	{
		blink_code( 1 );
		wait_sda_high( "before software reset" );
		printf( "STEP 1/3 cold start. Software reset in 3 s (PC17 %d)\n", sda_a_high() );
		Delay_Ms( 3000 );
		NVIC_SystemReset();
		while( 1 );
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
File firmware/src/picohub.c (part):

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 *   w stop feeding the watchdog (reset test)   h help
 *
 * Pin map = the board as fabricated (docs/spec.md section 3):
 *   PA0 A0 V_IN x11     PA4 A4 V_5V x11     PA5 A5 I_IN 0.5 V/A (+14 mA offset)
 *   PB1 A9 NTC TH1      PC0 A10 / PC3 A13 J2 CC1/CC2 sense, x2
 *   PB3 PICO_RUN (open-drain only)   PB4 MEZZ_EN (pull-down, drive high = on)
 *   PB6 EN_B (pull-up, drive low = off)   PB7 EN_BUCK (self-starts, drive low = off)
 *   PB8 MEZZ_PRESENT (low = present)   PB9 MEZZ_FAULT (low = fault)
 *   PB10 EN_USB (pull-down, drive high = on)   PB11 EN_A (pull-up)   PB12 LED_K (active low)
 *   PC14/PC15 USB-PD CC1/CC2 (external 5.1 k Rd)   PC16/PC17 I2C bus A (not used yet)
 */
#include "ch32fun.h"
#include <stdbool.h>
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#define OC_RECOVER_MS       5000  // ... for this long -> loads return
#define T_HOT_ON             750  // 0.1 C: notice "hot"
#define T_HOT_OFF            700
#define T_SHED_ON            850  // shed J2 + MEZZ_EN
#define T_SHED_OFF           750
#define T_CRIT_ON            950  // buck off
#define T_CRIT_OFF           700
#define D8_SHEDS               3  // this many temperature sheds ...
#define D8_WINDOW_MS      600000  // ... within 10 minutes -> MEZZ_EN stays off until cleared
#define V5_UNDER_MV         4400  // 5 V rail under-voltage (not on a 5 V-only source)
#define MEZZ_FAULT_HOLD_MS  1000  // MEZZ_EN returns this long after MEZZ_FAULT is released
#define CC_RD_MIN_MV         550  // J2 CC line (after the x2 divider) when a sink's Rd pulls it:
#define CC_RD_MAX_MV        1500  //   ~0.9 V; empty socket ~4 V, cable Ra ~0.2 V
#define SINK_ATTACH_MS       100  // USB-C tCCDebounce
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} hub;

// ------------------------------------------------------------------ pins
#define P_PICO_RUN     PB3
#define P_MEZZ_EN      PB4
#define P_EN_B         PB6
#define P_EN_BUCK      PB7
#define P_MEZZ_PRESENT PB8
#define P_MEZZ_FAULT   PB9
#define P_EN_USB       PB10
#define P_EN_A         PB11
#define P_LED          PB12

#define CH_V_IN  0
#define CH_V_5V  4
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	ADC1->SAMPTR1 = 0x00FFFFFF;   // longest sample time: the dividers are 9.1 k / 23.5 k sources
	ADC1->SAMPTR2 = 0x3FFFFFFF;
	ADC1->CTLR2 |= ADC_ADON | ADC_EXTSEL;
	funPinMode( PA0, 0 ); funPinMode( PA4, 0 ); funPinMode( PA5, 0 );   // analog mode
	funPinMode( PB1, 0 ); funPinMode( PC0, 0 ); funPinMode( PC3, 0 );
}

static uint16_t adc_read( int ch )   // average of 16 conversions, 0..4095 (~0.3 ms)
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

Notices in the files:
firmware/bringup/bringup.c:
SPDX-License-Identifier: MIT
Copyright (c) 2026 noknok
